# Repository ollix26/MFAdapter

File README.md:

This provides a interface to connect micro floppy drives (26 pin connector - normal floppies) to standard computers, or to connect standard floppy drives to laptop 26-pin interfaces.
Connect molex only if the connected floppy is the laptop one.

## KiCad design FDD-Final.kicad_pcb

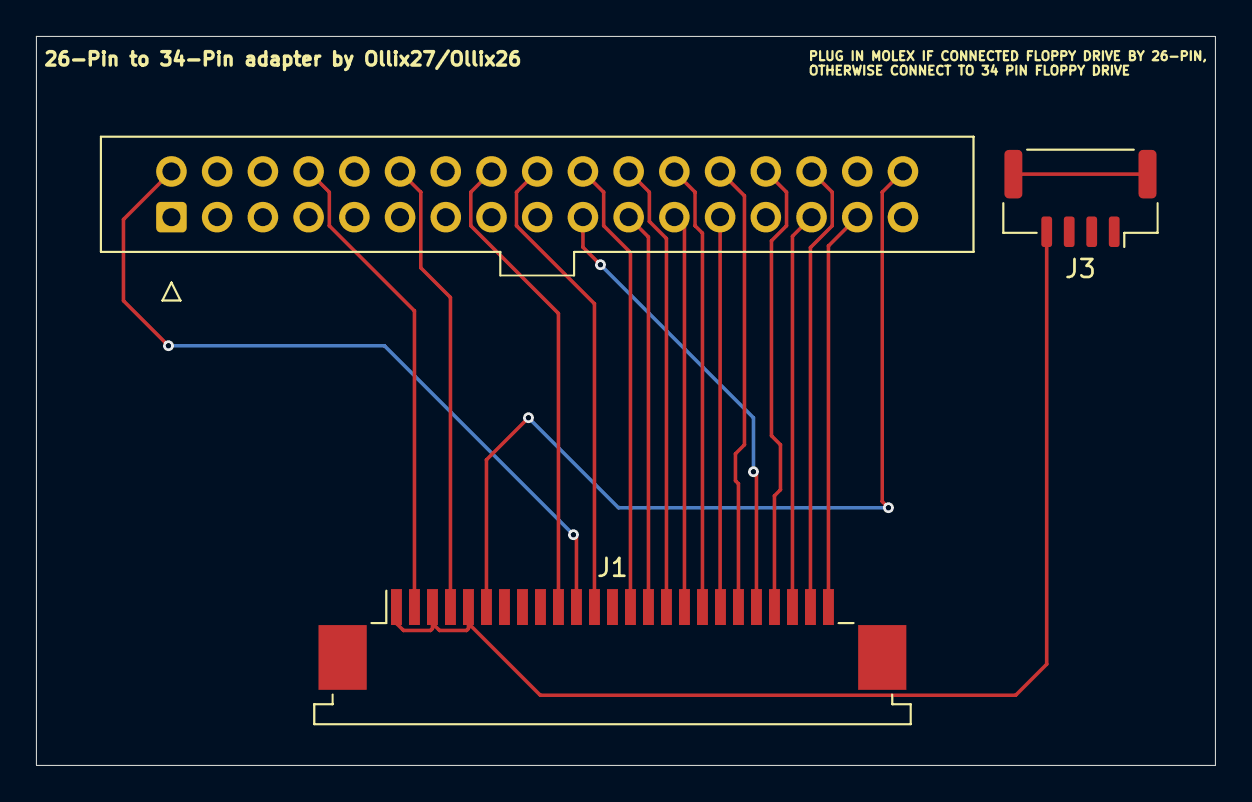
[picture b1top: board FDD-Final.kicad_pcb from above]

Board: 2 copper layers, 65.5 x 40.5 mm, 3 parts (0 on the bottom side), 15 nets.

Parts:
J1: Conn_01x26_Pin; TE_2-84952-5_1x25-1MP_P1.0mm_Horizontal
J2: Conn_02x17_Odd_Even_MountingPin; Floppy-Shugart-34-PIN
J3: Conn_01x04_MountingPin; Molex_CLIK-Mate_502386-0470_1x04-1MP_P1.25mm_Horizontal

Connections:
5V: J1.1, J1.3, J1.5, J3.4
DENSITY: J1.11, J2.2
DIRECTION: J1.12, J2.18
DISK CHANGE: J1.6, J2.34
DRIVE SELECT: J1.4, J2.12
GND: J1.15, J1.17, J1.21, J1.23, J1.25, J2.19, J2.21, J2.23, J2.29, J2.31
INDEX: J1.2, J2.8
MOTOR ENABLE: J1.10, J2.16
unnamed: J1.19, J2.25
READ DATA: J1.24, J2.30
STEP: J1.14, J2.20
TRACK 0: J1.20, J2.26
WRITE DATA: J1.16, J2.22
WRITE GATE: J1.18, J2.24
WRITE PROTECT: J1.22, J2.28

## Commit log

2026-02-17 Add Inital Files
2026-02-17 Add Gerber Files for manufacturing
